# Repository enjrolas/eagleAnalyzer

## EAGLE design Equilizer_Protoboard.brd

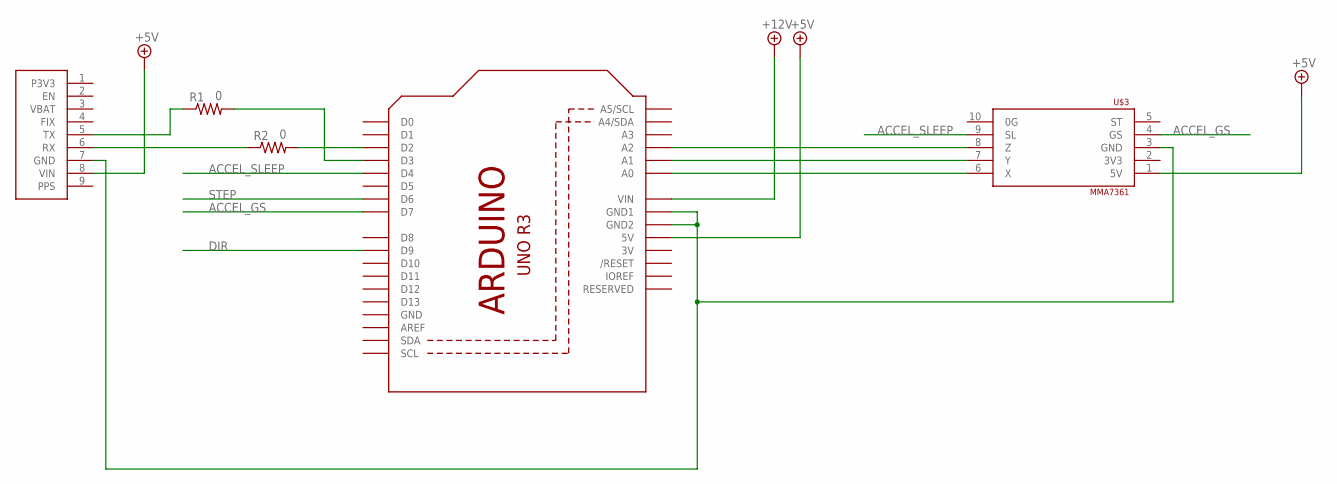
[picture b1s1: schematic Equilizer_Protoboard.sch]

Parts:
R1, R2: 0; 0204/7
U1: ARDUINOR3-BPLACE
U$3: MMA7361
U$4: ADAFRUIT_GPS_MODULE; ADAFRUIT_GPS_BREAKOUT

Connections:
3V: U1.3V
+5V: U1.5V, U$3.1 (5V), U$4.8 (VIN)
+12V: U1.VIN
ACCEL_GS: U1.D7, U$3.4 (GS)
ACCEL_SLEEP: U1.D4, U$3.9 (SL)
DIR: U1.D9
GND: U1.GND
unnamed: U1.GND1, U1.GND2, U$3.3 (GND), U$4.7 (GND)
unnamed: R2.1, U$4.6 (RX)
unnamed: R1.1, U$4.5 (TX)
unnamed: R1.2, U1.D3
unnamed: R2.2, U1.D2
unnamed: U1.A2, U$3.8 (Z)
unnamed: U1.A1, U$3.7 (Y)
unnamed: U1.A0, U$3.6 (X)
STEP: U1.D6

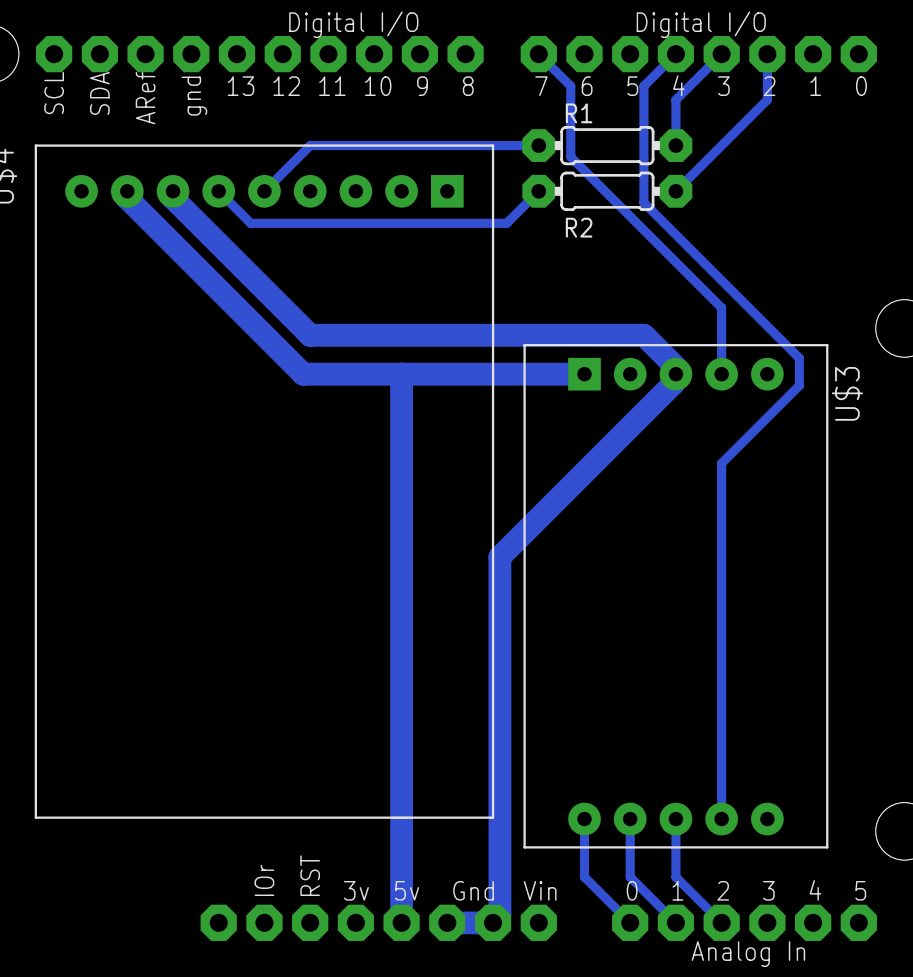
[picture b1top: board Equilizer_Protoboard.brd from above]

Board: 2 copper layers, 5 parts (0 on the bottom side), 11 nets.

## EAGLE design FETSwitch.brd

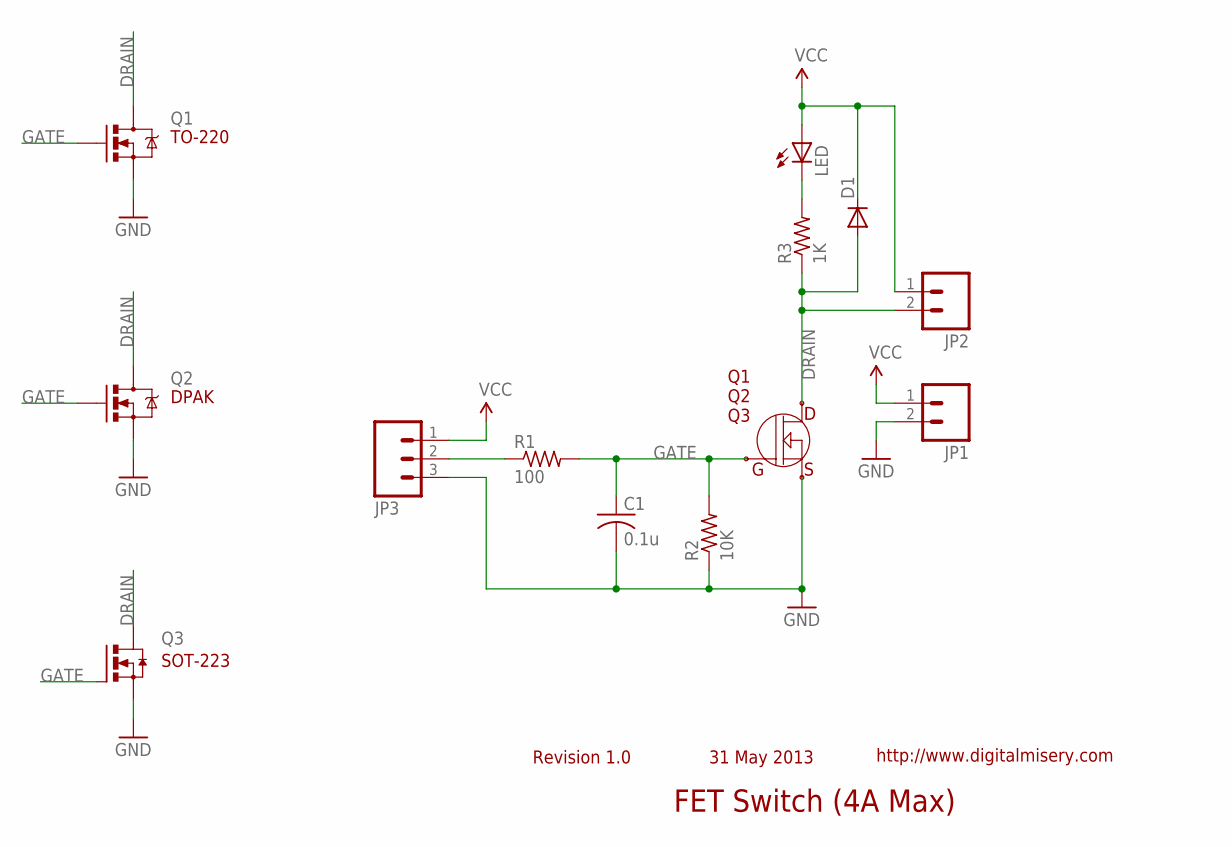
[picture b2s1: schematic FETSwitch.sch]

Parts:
C1: 0.1u; C0805K
D1: DIODESMA; SMA-DIODE
JP1, JP2: M02PTH3; 1X02_LONGPADS
JP3: M03LONGPADS; 1X03_LONGPADS
LED: LEDCHIP-LED0805; CHIP-LED0805
Q1: MOSFET-NCHANNELFQP30N06L; TO220V
Q2: MOSFET-NCHANNELFDD8780; DPAK
Q3: N-HEXFET-2D_SOT232-; SOT223
R1: 100; R0805
R2: 10K; R0805
R3: 1K; R0805

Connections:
DRAIN: D1.A, JP2.2, Q1.2 (D), Q2.4 (D), Q3.2 (D), Q3.4 (D), R3.1
GATE: C1.1, Q1.1 (G), Q2.1 (G), Q3.1 (G), R1.2, R2.2
GND: C1.2, JP1.2, JP3.3, Q1.3 (S), Q2.3 (S), Q3.3 (S), R2.1
unnamed: LED.C, R3.2
unnamed: JP3.2, R1.1
VCC: D1.C, JP1.1, JP2.1, JP3.1, LED.A

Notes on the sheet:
TO-220
DPAK
SOT-223
31 May 2013
http://www.digitalmisery.com
FET Switch (4A Max)
Revision 1.0
Q1 Q2 Q3

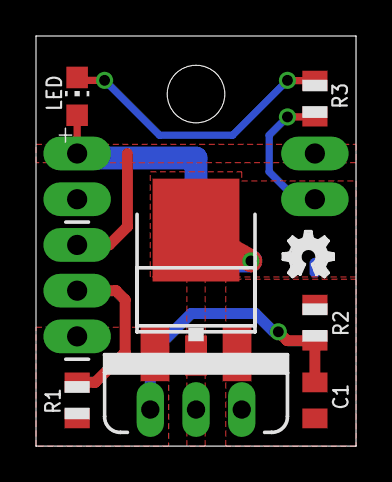
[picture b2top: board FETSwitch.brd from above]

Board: 2 copper layers, 17.8 x 22.8 mm, 13 parts (1 on the bottom side), 6 nets.

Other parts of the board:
U$2: OSHW_FILLX100_NOTEXT

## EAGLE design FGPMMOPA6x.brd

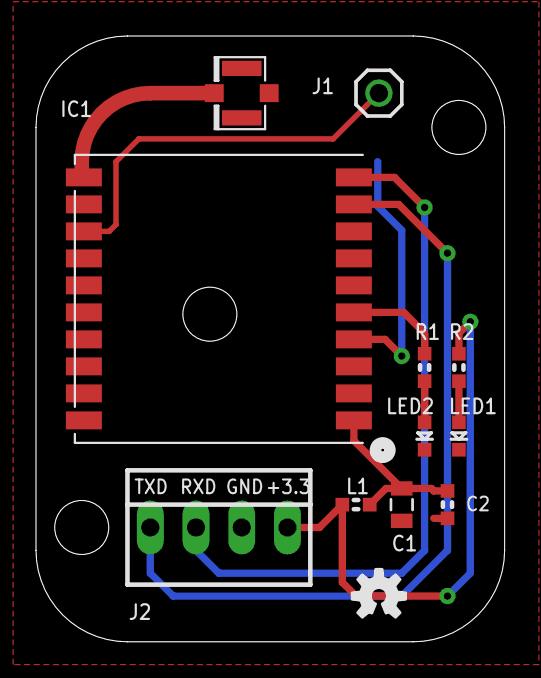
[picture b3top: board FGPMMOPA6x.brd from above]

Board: 2 copper layers, 26.0 x 33.7 mm, 13 parts (1 on the bottom side), 11 nets.

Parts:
B1: Keystone 3000; BATTCON_12MM
C1: 10µF; 0805
C2: 100nF; 0603
IC1: FGPMMOPA6H
J1: PPS; 1X01
J2: Interface; 22-23-2041
J3: U.FL
L1: Bead; 0603
LED1: Power; LED-0603
LED2: Status; LED-0603
R1, R2: 1kΩ; 0603
SY: OSHW-LOGOS; OSHW-LOGO-S

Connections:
+3V3: J2.4, L1.2, R2.2
GND: B1.GND, C1.1, C2.1, IC1.P$3, IC1.P$8, IC1.P$12, IC1.P$19, J2.3, J3.P$1, J3.P$2, LED1.C, LED2.C
unnamed: C1.2, C2.2, IC1.P$1, L1.1
unnamed: B1.PWR@1, IC1.P$4
unnamed: IC1.P$5, R1.2
unnamed: IC1.P$9, J2.1
unnamed: IC1.P$10, J2.2
unnamed: IC1.P$13, J1.1
unnamed: IC1.P$11, J3.P$3
unnamed: LED2.A, R1.1
unnamed: LED1.A, R2.1

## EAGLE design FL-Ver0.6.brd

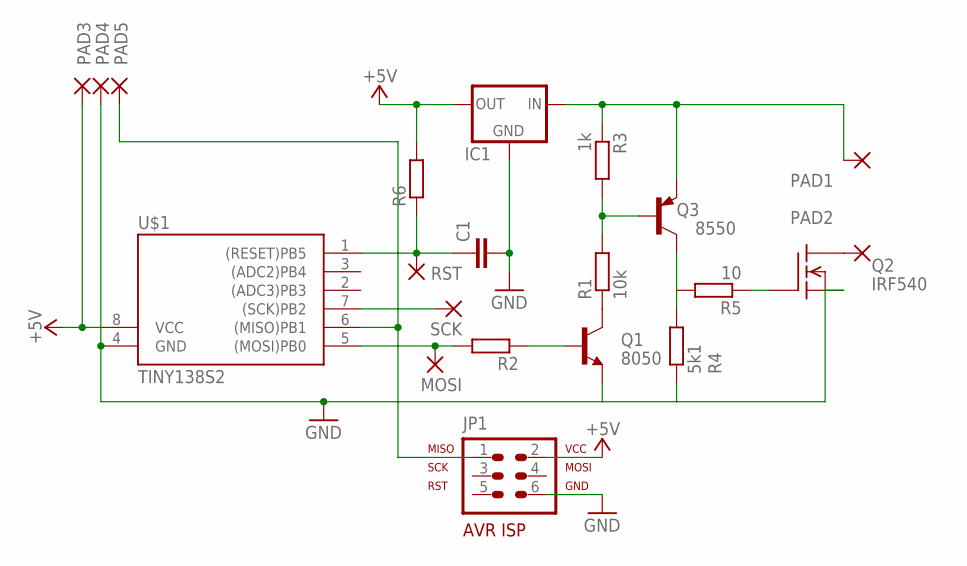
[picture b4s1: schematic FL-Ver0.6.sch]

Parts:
C1: C-EUC0805; C0805
IC1: 78MXXSDPACK; DPACK
JP1: AVR-ISP-6VERT; AVR-ISP-6
MOSI: 1,6/0,8
PAD1, PAD2, PAD3, PAD4, PAD5: SMD5; SMD2,54-5,08
Q1: 8050; TO92-EBC
Q2: IRF540; TO220
Q3: 8550; TO92-EBC
R1: 10k; 0309/12
R2: R-EU_0309/12; 0309/12
R3: 1k; 0309/12
R4: 5k1; 0309/12
R5: 10; 0309/12
R6: R-EU_M0805; M0805
RST: 1,6/0,8
SCK: 1,6/0,8
U$1: TINY138S2; SO08

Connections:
+5V: IC1.3 (OUT), JP1.2, PAD3.1, R6.2, U$1.8 (VCC)
GND: C1.2, IC1.2 (GND), JP1.6, PAD4.1, Q1.E, Q2.3 (S), R4.1, U$1.4 (GND)
unnamed: Q2.1 (G), R5.1
unnamed: SCK.1, U$1.7 ((SCK)PB2)
unnamed: Q1.B, R2.1
unnamed: C1.1, R6.1, RST.1, U$1.1 ((RESET)PB5)
unnamed: PAD2.1, Q2.2 (D)
unnamed: Q1.C, R1.1
unnamed: Q3.B, R1.2, R3.2
unnamed: Q3.C, R4.2, R5.2
unnamed: JP1.1, PAD5.1, U$1.6 ((MISO)PB1)
unnamed: IC1.1 (IN), PAD1.1, Q3.E, R3.1
unnamed: MOSI.1, R2.2, U$1.5 ((MOSI)PB0)

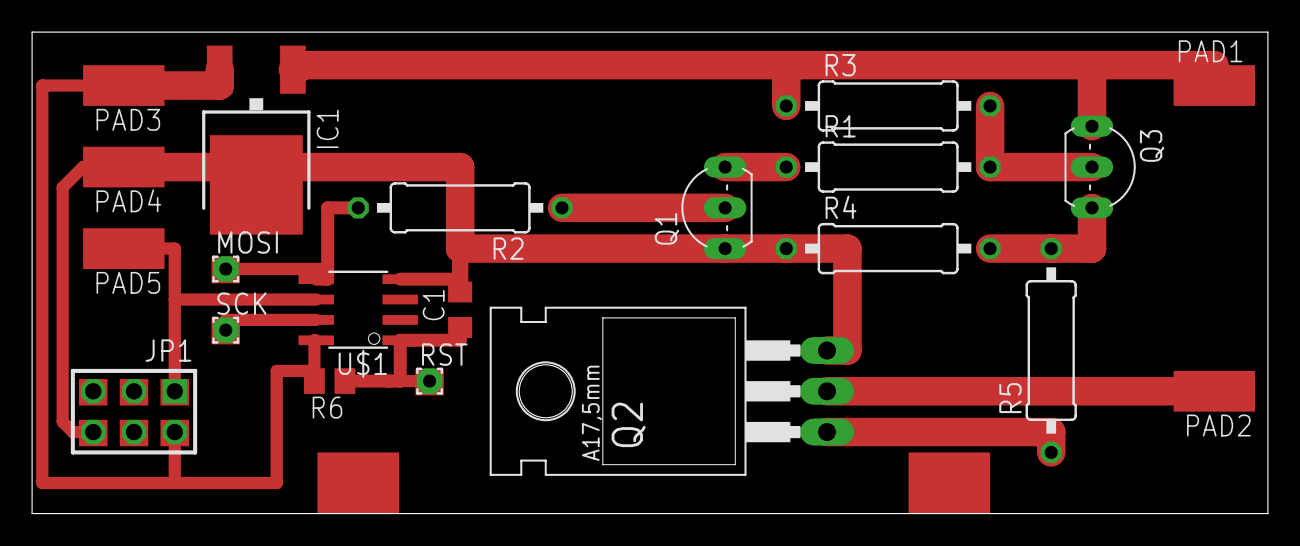
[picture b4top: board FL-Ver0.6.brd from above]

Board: 2 copper layers, 77.0 x 30.0 mm, 21 parts (0 on the bottom side), 13 nets.

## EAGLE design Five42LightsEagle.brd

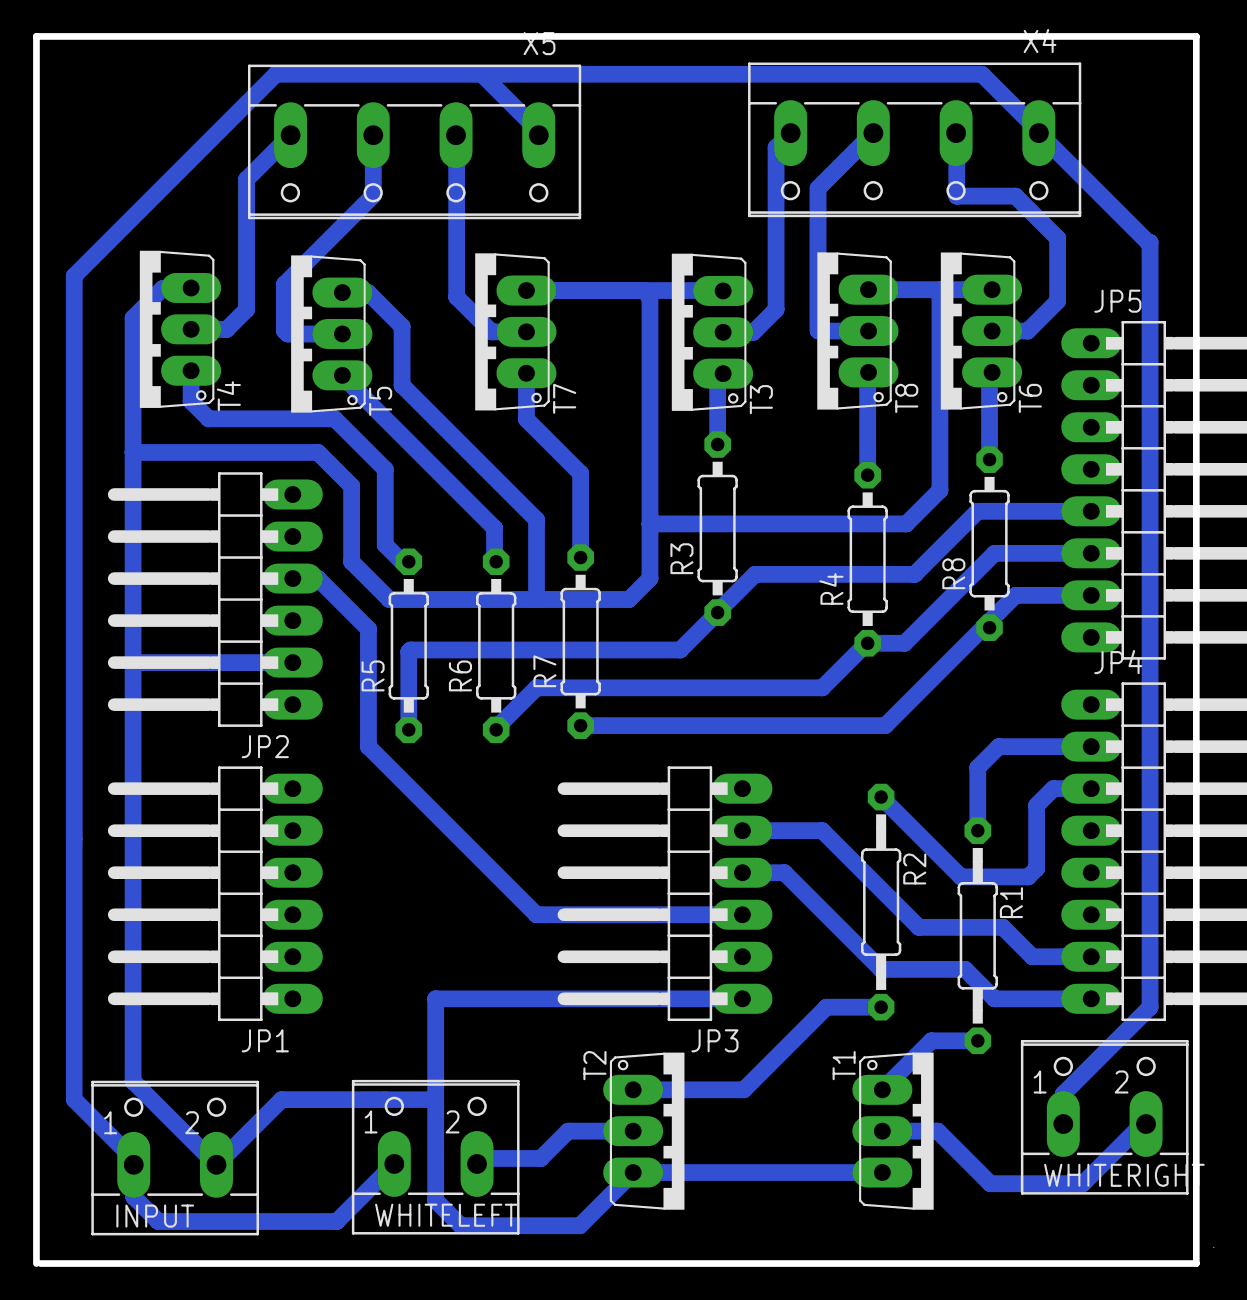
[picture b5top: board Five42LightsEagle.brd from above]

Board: 2 copper layers, 71.2 x 74.2 mm, 26 parts (0 on the bottom side), 26 nets.

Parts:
INPUT: W237-102
JP1, JP2, JP3: 1X06/90
JP4, JP5: 1X08/90
R1, R2: 2.2k; 0207/12
R3, R4, R5, R6, R7, R8: 2.2k; 0207/10
T1, T2, T3, T4, T5, T6, T7, T8: 2SC1944; T-30_V
WHITELEFT: W237-102
WHITERIGHT: W237-102
X4, X5: W237-4

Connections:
GND: INPUT.2, JP2.2, JP3.1, T1.3, T2.3, T3.3, T4.3, T5.3, T6.3, T7.3, T8.3
unnamed: R2.2, T2.1
unnamed: R1.2, T1.1
unnamed: R3.2, T3.1
unnamed: R4.2, T8.1
unnamed: R8.2, T6.1
unnamed: R7.2, T7.1
unnamed: R6.2, T5.1
unnamed: R5.2, T4.1
unnamed: T1.2, WHITERIGHT.2
unnamed: JP5.5, R3.1, R5.1
unnamed: INPUT.1, WHITELEFT.1, WHITERIGHT.1, X4.1, X5.1
unnamed: T2.2, WHITELEFT.2
unnamed: T4.2, X5.4
unnamed: JP5.6, R4.1, R6.1
unnamed: JP5.7, R7.1, R8.1
unnamed: T5.2, X5.3
unnamed: T7.2, X5.2
unnamed: JP4.3, R2.1
unnamed: JP4.2, R1.1
unnamed: T6.2, X4.2
unnamed: T8.2, X4.3
unnamed: T3.2, X4.4
unnamed: JP2.4, JP3.3
unnamed: JP3.4, JP4.8
unnamed: JP3.5, JP4.7

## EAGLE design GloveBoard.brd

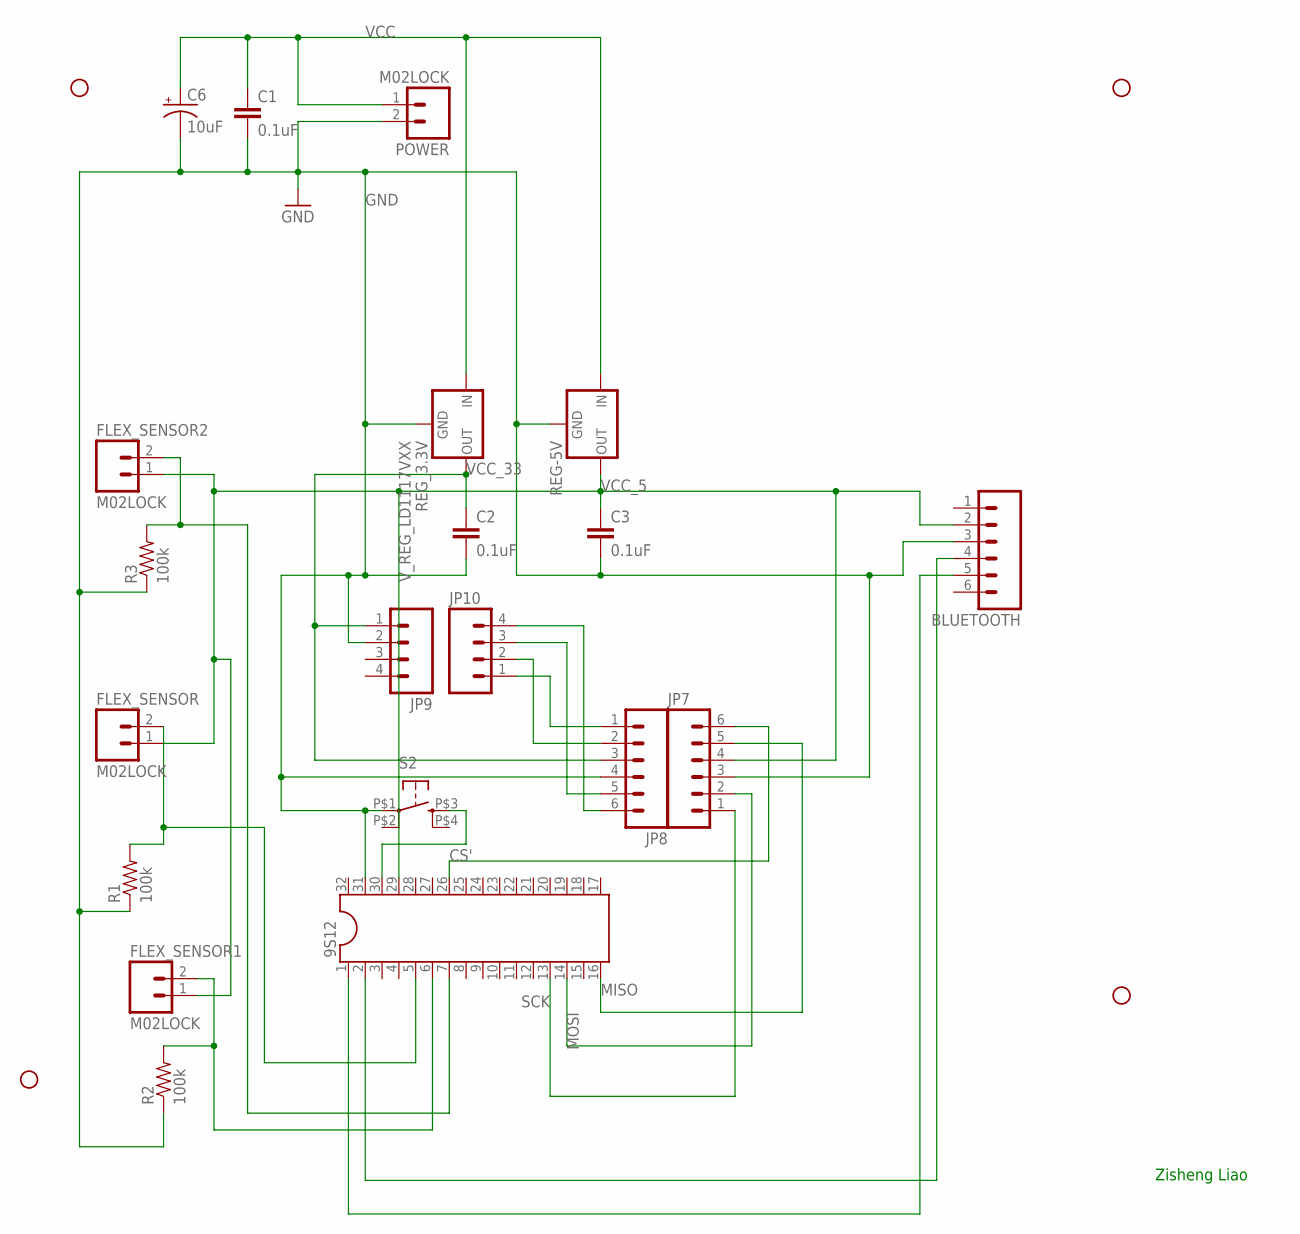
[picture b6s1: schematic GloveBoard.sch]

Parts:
9S12: DIL32
BLUETOOTH: M06LOCK_LONGPADS; 1X06_LOCK_LONGPADS
C1, C2, C3: 0.1uF; CAP-PTH-SMALL-KIT
C6: 10uF; CPOL-RADIAL-10UF-25V
FLEX_SENSOR, FLEX_SENSOR1, FLEX_SENSOR2: M02LOCK; 1X02_LOCK
JP7, JP8: M06LOCK_LONGPADS; 1X06_LOCK_LONGPADS
JP9, JP10: M04PTH; 1X04
POWER: M02LOCK; 1X02_LOCK
R1, R2, R3: 100k; AXIAL-0.3-KIT
REG-5V: V_REG_78XX-TO-220; TO-220-ALT
REG_3.3V: V_REG_LD1117VXX; 78XXL
S2: TAC_SWITCHKSA_SEALED; KSA_SEALED_TAC_SWITCH
STANDOFF1, STANDOFF2, STANDOFF3, STANDOFF4: STAND-OFF

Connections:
CS': 9S12.26, JP7.6
GND: 9S12.31, BLUETOOTH.3, C1.2, C2.2, C3.2, C6.2 (-), JP7.3, JP8.4, JP9.2, POWER.2, R1.P$1 (1), R2.P$1 (1), R3.P$1 (1), REG-5V.GND, REG_3.3V.IN (GND), S2.P$1 (1)
MISO: 9S12.16, JP7.5
MOSI: 9S12.14, JP7.2
unnamed: JP8.2, JP10.2
unnamed: JP8.1, JP10.1
unnamed: JP8.5, JP10.3
unnamed: JP8.6, JP10.4
unnamed: 9S12.6, FLEX_SENSOR1.2, R2.P$2 (2)
unnamed: 9S12.7, FLEX_SENSOR2.2, R3.P$2 (2)
unnamed: 9S12.30, S2.P$3 (3)
unnamed: 9S12.1, BLUETOOTH.5
unnamed: 9S12.2, BLUETOOTH.4
unnamed: 9S12.5, FLEX_SENSOR.2, R1.P$2 (2)
SCK: 9S12.13, JP7.1
VCC: C1.1, C6.1 (+), POWER.1, REG-5V.IN, REG_3.3V.OUT (IN)
VCC_5: 9S12.29, BLUETOOTH.2, C3.1, FLEX_SENSOR.1, FLEX_SENSOR1.1, FLEX_SENSOR2.1, JP7.4, REG-5V.OUT
VCC_33: C2.1, JP8.3, JP9.1, REG_3.3V.GND (OUT)

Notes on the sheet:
Zisheng Liao

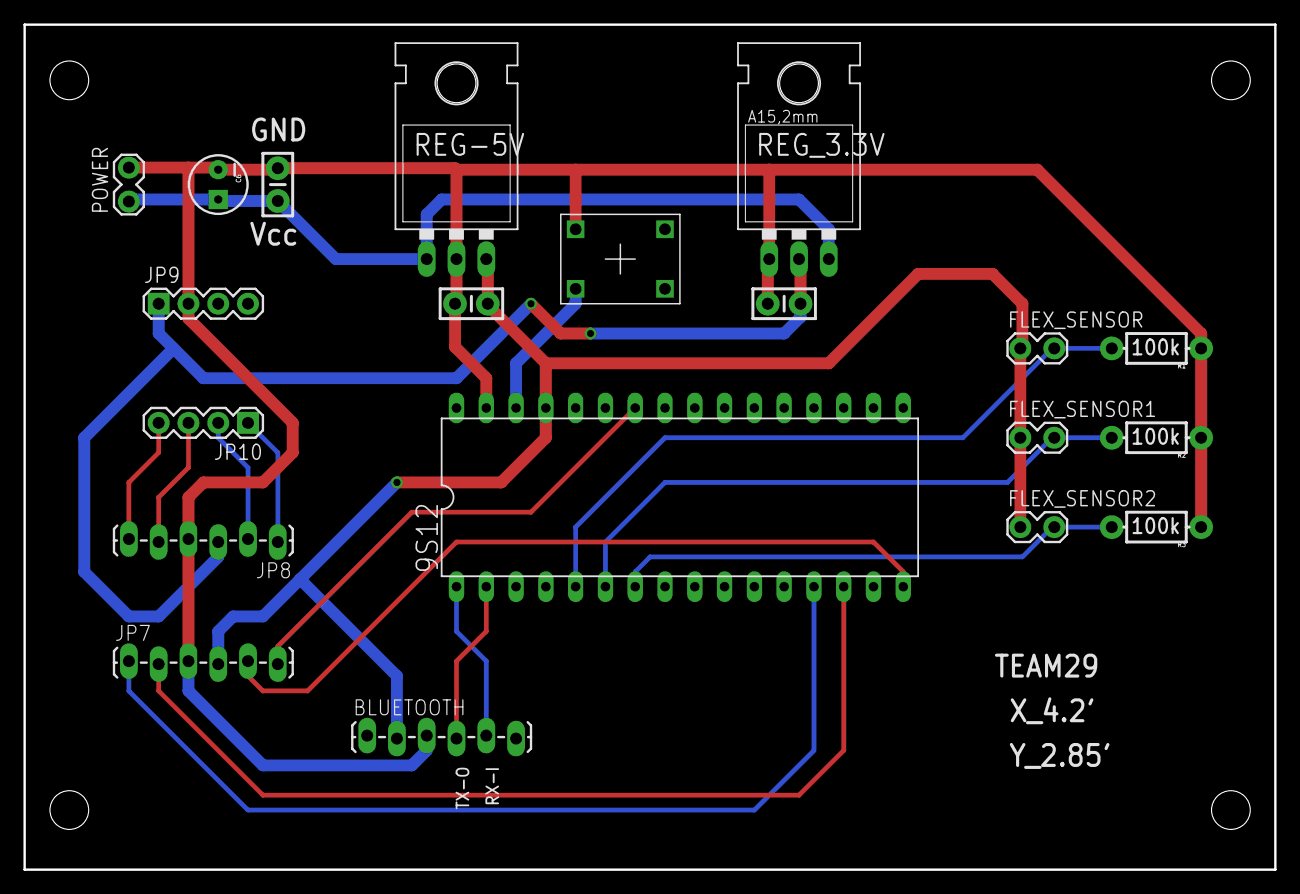
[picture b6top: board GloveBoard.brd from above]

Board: 2 copper layers, 106.7 x 72.1 mm, 24 parts (0 on the bottom side), 18 nets.

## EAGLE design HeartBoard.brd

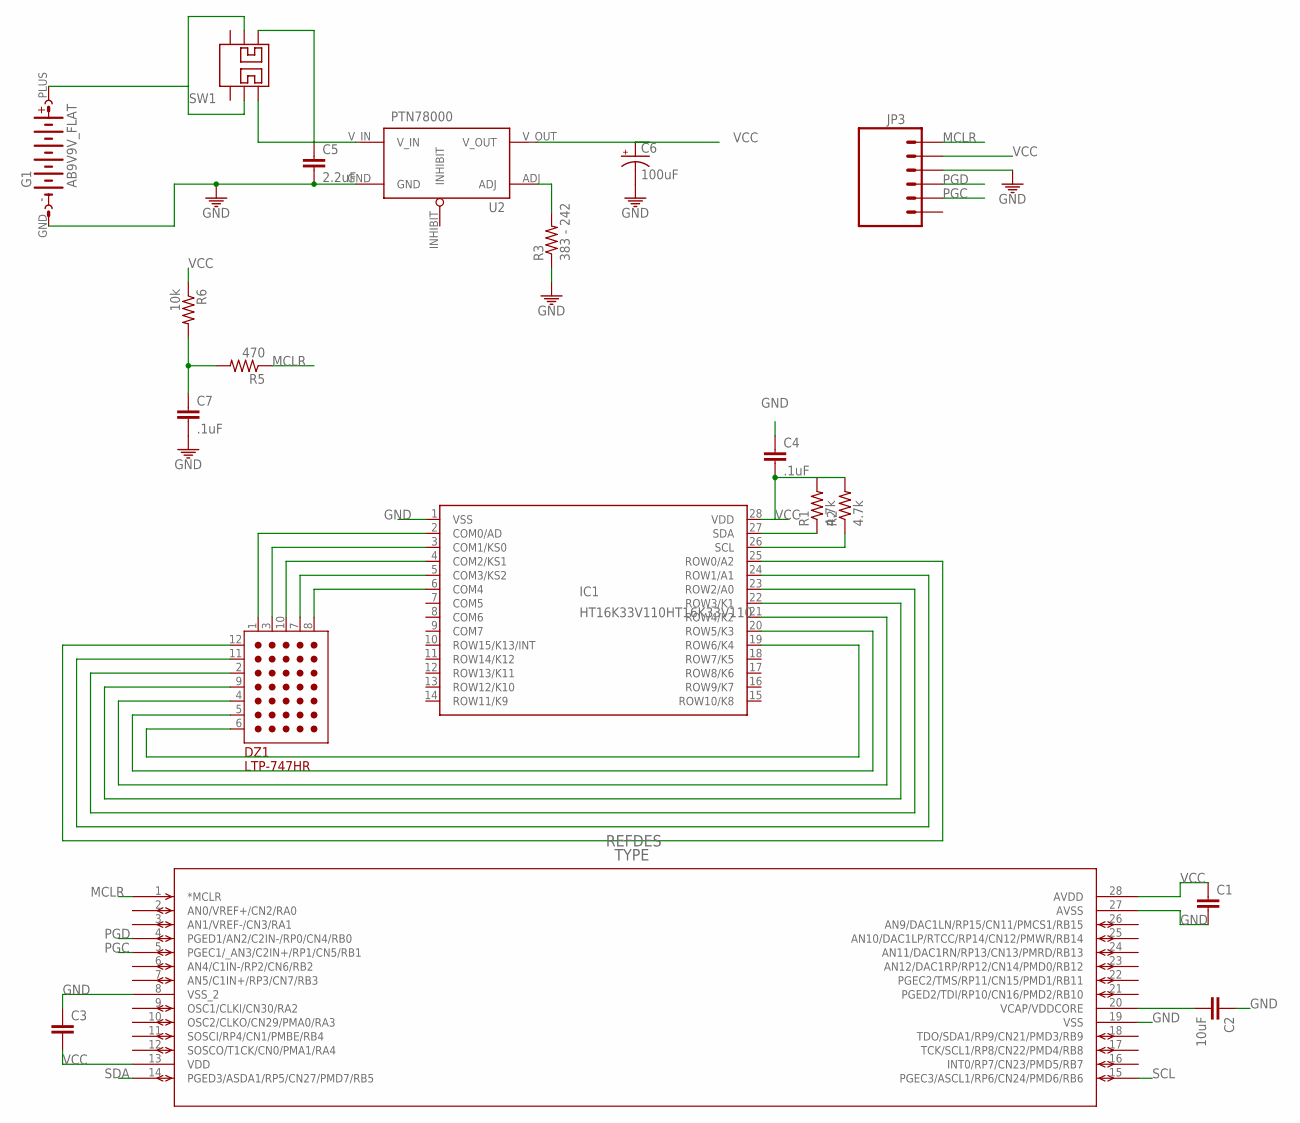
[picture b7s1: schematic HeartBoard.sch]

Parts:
C1, C3: CAP1206; 1206
C2: 10uF; 1206
C4, C7: .1uF; 1206
C5: 2.2uF; 1206
C6: 100uF; CPOL-RADIAL-100UF-25V
DZ1: LTP-747HR
G1: AB9V9V_FLAT; BH9VPC
IC1: HT16K33V110HT16K33V110; SOP28
JP3: M06LOCK; 1X06_LOCK
R1, R2: 4.7k; 0805
R3: 383 - 242; 0805
R5: 470; 0805
R6: 10k; 0805
SW1: SLIDE_SWITCH_DPDTTOP; EG2207
U2: PTN78000
U$1: DSPIC33FJ64GP802; SOIC28-W_MC

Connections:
GND: C1.2, C2.1, C3.1, C4.1, C5.2, C6.2 (-), C7.2, G1.GND (-), IC1.1 (VSS), JP3.3, R3.1, U2.GND, U$1.8 (VSS_2), U$1.19 (VSS), U$1.27 (AVSS)
MCLR: JP3.1, R5.1, U$1.1 (*MCLR)
unnamed: DZ1.1 (C1), IC1.2 (COM0/AD)
unnamed: C7.1, R5.2, R6.2
unnamed: C2.2, U$1.20 (VCAP/VDDCORE)
unnamed: G1.PLUS (+), SW1.P$2, SW1.P$5
unnamed: R3.2, U2.ADJ
unnamed: DZ1.3 (C2), IC1.3 (COM1/KS0)
unnamed: DZ1.10 (C3), IC1.4 (COM2/KS1)
unnamed: DZ1.7 (C4), IC1.5 (COM3/KS2)
unnamed: DZ1.8 (C5), IC1.6 (COM4)
unnamed: DZ1.12 (R1), IC1.25 (ROW0/A2)
unnamed: DZ1.11 (R2), IC1.24 (ROW1/A1)
unnamed: DZ1.2 (R3), IC1.23 (ROW2/A0)
unnamed: DZ1.9 (R4), IC1.22 (ROW3/K1)
unnamed: DZ1.4 (R5), IC1.21 (ROW4/K2)
unnamed: DZ1.5 (R6), IC1.20 (ROW5/K3)
unnamed: DZ1.6 (R7), IC1.19 (ROW6/K4)
PGC: JP3.5, U$1.5 (PGEC1/_AN3/C2IN+/RP1/CN5/RB1)
PGD: JP3.4, U$1.4 (PGED1/AN2/C2IN-/RP0/CN4/RB0)
PVDD: C5.1, SW1.P$1, SW1.P$4, U2.V_IN
SCL: IC1.26 (SCL), R2.1, U$1.15 (PGEC3/ASCL1/RP6/CN24/PMD6/RB6)
SDA: IC1.27 (SDA), R1.1, U$1.14 (PGED3/ASDA1/RP5/CN27/PMD7/RB5)
VCC: C1.1, C3.2, C4.2, C6.1 (+), IC1.28 (VDD), JP3.2, R1.2, R2.2, R6.1, U2.V_OUT, U$1.13 (VDD), U$1.28 (AVDD)

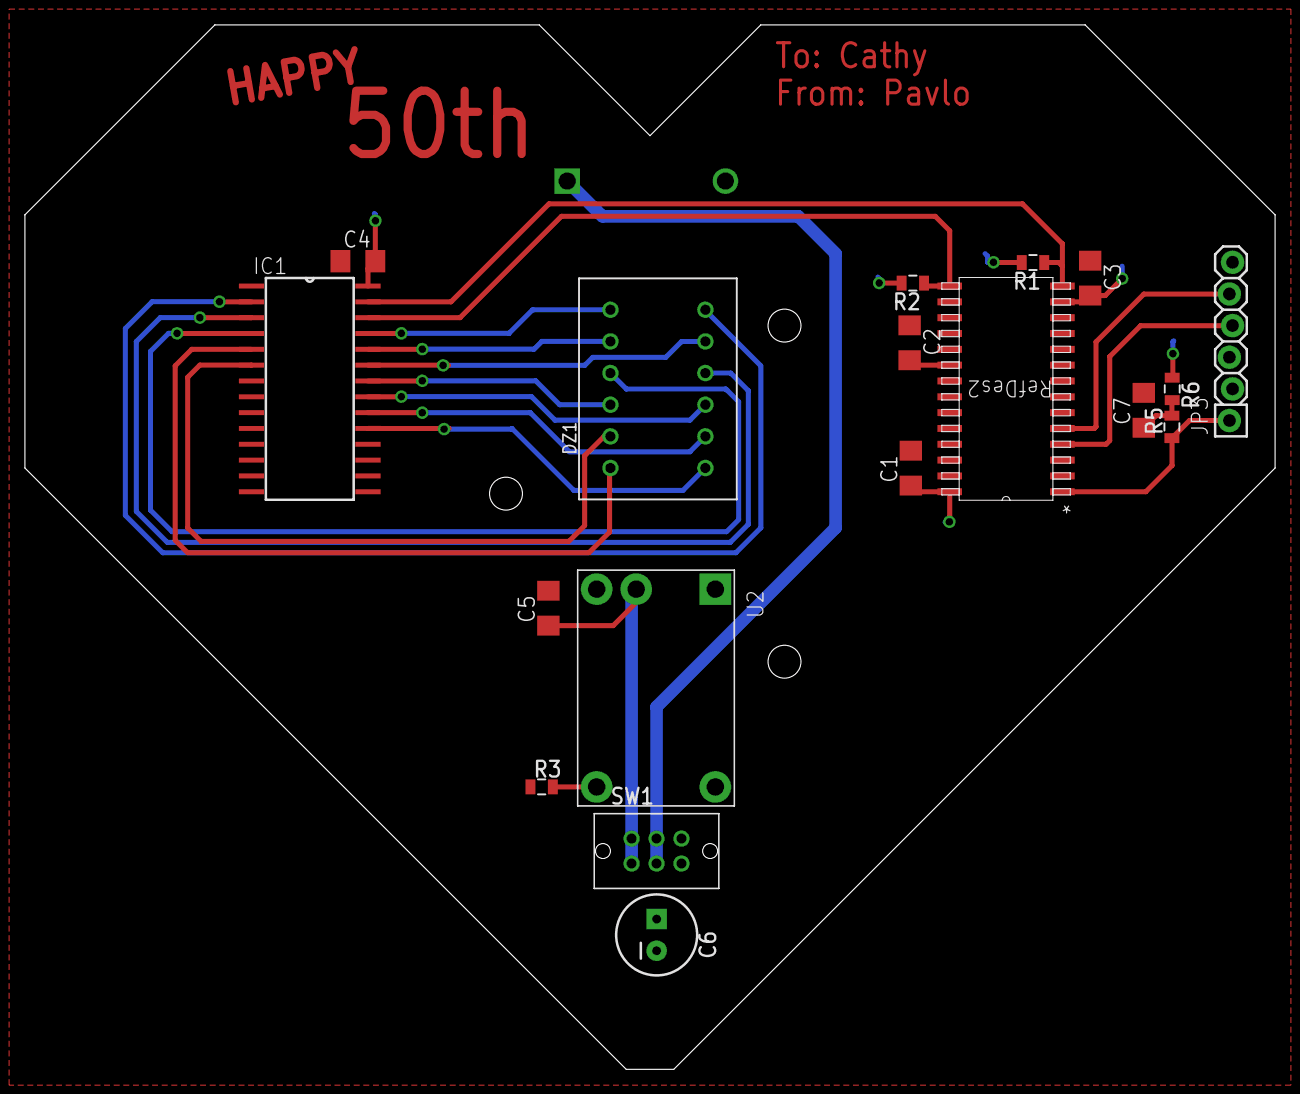
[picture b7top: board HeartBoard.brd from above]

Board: 2 copper layers, 100.3 x 83.8 mm, 19 parts (1 on the bottom side), 24 nets.

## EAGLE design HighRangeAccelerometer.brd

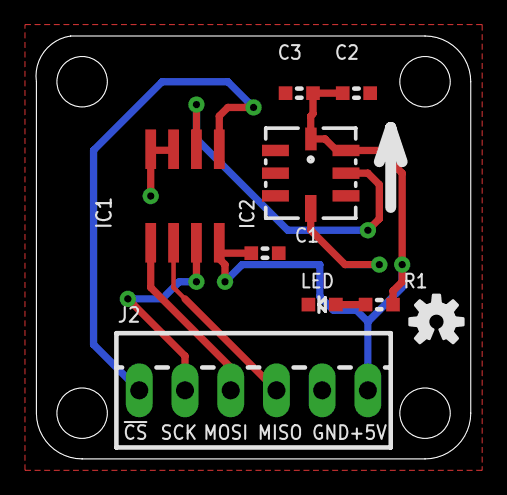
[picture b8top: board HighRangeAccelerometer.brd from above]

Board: 2 copper layers, 24.2 x 23.5 mm, 10 parts (1 on the bottom side), 9 nets.

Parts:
C1, C2: 100nF; 0603
C3: 1µF; 0603
IC1: MCP3202-CI/SN; SO-08
IC2: AD22282-A-R2; ADXL193
J1: Self-test; SJ
J2: Interface; 22-23-2061
LED: Power; LED-0603
R1: 1kΩ; 0603
SY: OSHW-LOGOS; OSHW-LOGO-S

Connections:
+5V: C1.2, C2.2, C3.2, IC1.8, IC2.P$7, IC2.P$8, J1.2, J2.6, R1.2
GND: C1.1, C2.1, C3.1, IC1.3, IC1.4, IC2.P$3, J2.5, LED.C
unnamed: IC1.2, IC2.P$6
unnamed: LED.A, R1.1
unnamed: IC1.6, J2.4
unnamed: IC1.5, J2.3
unnamed: IC1.7, J2.2
unnamed: IC1.1, J2.1
unnamed: IC2.P$4, J1.1

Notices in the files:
parts and their libraries:
SparkFun-Connectors: Licensing: CC v3.0 Share-Alike You are welcome to use this library for commercial purposes.
